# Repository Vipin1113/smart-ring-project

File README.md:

# Compact BLE-Based Smart Ring PCB for Health Monitoring and Gesture Detection

## Overview

This repository contains the complete KiCad project files, PCB layouts, schematic designs, manufacturing outputs, and documentation for a compact BLE-enabled Smart Ring developed for health monitoring and gesture detection applications.

The project focuses on wearable-oriented PCB miniaturization, low-power BLE communication, physiological sensing, gesture detection, RF-aware PCB implementation, and compact embedded system integration within a smart-ring-compatible form factor.

The implemented smart ring integrates:

- Nordic nRF52810 BLE SoC
- MAX30102 PPG Sensor
- ICM-42670 IMU Sensor
- Li-ion Charging Subsystem
- 3.3V Power Regulation
- Compact BLE Antenna Implementation

The final PCB dimensions achieved are:

22.8 mm × 9.6 mm

---

# Project Features

- Bluetooth Low Energy (BLE) Communication
- Heart Rate Monitoring
- SpO2 Monitoring
- Gesture Detection
- Motion Tracking
- Rechargeable Li-ion Battery Support
- Compact Wearable PCB Architecture
- RF Antenna Keepout Implementation
- Compact SWD Debugging Pads
- Exposed Charging Pads
- Backside PPG Sensor Placement
- 0402 Passive Component Integration

---

# Hardware Components

| Component | Manufacturer | Part Number |
|---|---|---|
| BLE MCU | Nordic Semiconductor | nRF52810-QCAA-T |
| PPG Sensor | Analog Devices | MAX30102 |
| IMU Sensor | TDK InvenSense | ICM-42670-P |
| Battery Charging IC | Microchip Technology | MCP73831-2-OT |
| 3.3V LDO | Texas Instruments | TPS78233DDC |
| 32 MHz Crystal | ECS Inc. | ECS-320-8-37-CKM-TR |
| 2.4 GHz Antenna | Johanson Technology | 2450AT18A100E |

---

# PCB Miniaturization and Design Evolution

The initial smart ring implementation utilized a larger PSoC BLE module-based architecture which occupied approximately:

30.4 mm × 12.0 mm

Although the module simplified BLE integration, it significantly increased PCB area and routing constraints.

To improve compactness and wearable compatibility, the architecture was migrated to the Nordic nRF52810 BLE SoC in a compact QFN package.

After multiple PCB iterations and routing optimizations, the final PCB dimensions were successfully reduced to:

22.8 mm × 9.6 mm

Major optimizations implemented include:

- Migration from BLE module to compact QFN SoC
- Compact exposed SWD pads
- Exposed charging pads
- Compact battery solder pads
- 0402 passive components
- Backside PPG placement
- RF antenna keepout implementation
- Routing optimization
- Compact subsystem placement
- Improved RF-aware PCB design

---

# PCB Design Highlights

## BLE Processing Subsystem

- Nordic nRF52810 BLE SoC
- ARM Cortex-M4
- BLE communication support
- Low-power wearable operation
- Compact QFN package

## Physiological Sensing

- MAX30102 optical PPG sensor
- Heart-rate monitoring
- SpO2 monitoring
- Backside wearable placement

## Motion Sensing

- ICM-42670 6-axis IMU
- Gesture detection
- Motion tracking
- Activity monitoring

## Power Management

- MCP73831 Li-ion charging IC
- TPS78233 low-noise LDO
- Rechargeable Li-ion battery support

## RF Subsystem

- 2.4 GHz chip antenna
- RF matching network
- Dedicated antenna keepout region

---

# Industrial-Level Miniaturization Considerations

Commercial smart-ring products generally utilize advanced packaging and PCB technologies including:

- WLCSP (Wafer-Level Chip Scale Packaging)
- HDI PCB technology
- Blind and buried vias
- Microvia routing
- Flexible PCB structures
- System-in-Package (SiP) integration
- Ultra-miniature PMIC solutions

Industrial wearable PMIC solutions analyzed during this project include:

- TI BQ25120A
- Nordic nPM1300
- Dialog DA9070
- MAX20345

These PMICs integrate:

- Battery charging
- Multiple LDOs
- Buck/boost converters
- Battery protection
- Fuel gauging

within a single compact package.

Although such PMICs can significantly reduce PCB area, they introduce substantially higher routing complexity and manufacturing difficulty. Therefore, a simpler discrete charging and regulation architecture was selected for the current implementation.

---

# Repository Structure

smart-ring-project/

├── README.md

├── LICENSE

├── smart_ring.kicad_pro

├── smart_ring.kicad_sch

├── smart_ring.kicad_pcb

├── Gerbers/

├── Images/

├── Report/

└── Datasheets/

---

# PCB Images

## Root Schematic

## PCB Layout and Routing

## 3D PCB Top View

## 3D PCB Bottom View

---

# Software Used

- KiCad 8.0
- GitHub
- Overleaf
- IEEE Conference LaTeX Template

---

# Verification and Validation

The implemented smart ring PCB successfully passed:

- Electrical Rule Check (ERC)
- Design Rule Check (DRC)
- Footprint Verification
- Connectivity Validation

The design additionally incorporates:

- RF-aware antenna keepout implementation
- Ground-plane optimization
- Compact routing methodology
- Wearable-oriented subsystem placement

---

# Future Improvements

Future improvements may include:

- Firmware implementation
- Gesture-recognition algorithms
- Mobile application development
- Flexible PCB implementation
- HDI PCB technology
- WLCSP packaging
- Advanced PMIC integration
- Battery-life optimization

---

# License

This project is licensed under the MIT License.

See the LICENSE file for details.

---

# Author

Vipin Kumar Mishra  
M.Tech ECE (VLSI)  
IIIT Bangalore

---

# Acknowledgement

This project was developed as part of the Electronic Systems Packaging course project focusing on compact wearable embedded system design, PCB miniaturization, RF-aware layout implementation, and smart wearable hardware development.

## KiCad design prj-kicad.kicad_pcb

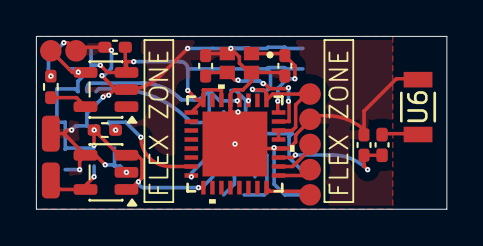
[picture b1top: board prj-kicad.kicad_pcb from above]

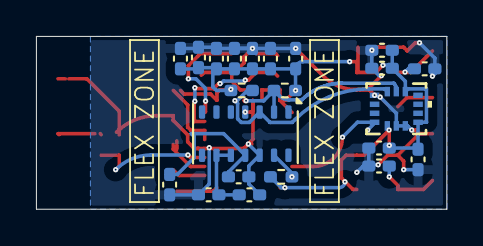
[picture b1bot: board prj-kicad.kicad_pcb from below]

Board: 2 copper layers, 22.8 x 9.6 mm, 38 parts (22 on the bottom side), 18 nets.

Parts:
C1, C2, C3, C15, C21: 1u; C_0402_1005Metric_Pad0.74x0.62mm_HandSolder
C4, C8, C17: 4.7u; C_0402_1005Metric_Pad0.74x0.62mm_HandSolder
C5, C6, C7, C10, C11, C14, C16, C18, C19, C22: 0.1u; C_0402_1005Metric_Pad0.74x0.62mm_HandSolder
C9: 0.8p; C_0402_1005Metric_Pad0.74x0.62mm_HandSolder
C12, C13: 12p; C_0402_1005Metric_Pad0.74x0.62mm_HandSolder
J1, J2: Conn_01x01; SolderWirePad_1x01_SMD_1x2mm
J3: Conn_01x02; Charging_Pad
J4: Conn_01x05; SWD_Pad
L1: 3.9n; L_0402_1005Metric_Pad0.77x0.64mm_HandSolder
R1: 40K; R_0402_1005Metric_Pad0.72x0.64mm_HandSolder
R4, R8: 10K; R_0402_1005Metric_Pad0.72x0.64mm_HandSolder
R6, R7: 4.7K; R_0402_1005Metric_Pad0.72x0.64mm_HandSolder
U1: MCP73831-2-OT; SOT-23-5
U2: NRF52810-QCAA-T; QFN32_5X5_NOR
U3: ICM-42670-P; LGA14_2.5X3X0.76_IVS
U4: TPS78233DDC; SOT-23-5
U5: MAX30102; Maxim_OLGA-14_3.3x5.6mm_P0.8mm
U6: 2450AT18A100E; 2450AT18A100E_JOT
Y2: ECS-320-8-37-CKM-TR; XTAL_ECS-320-8-37-CKM-TR

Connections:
/IMU/3p3V: C2.1, C4.1, C5.1, C6.2, C10.2, C11.2, C14.2, C17.2, C18.2, C19.2, C21.2, C22.2, J4.5, R4.1, R6.1, R7.1, R8.2, U1.3 (V_{BAT}), U2.1 (DEC1), U2.9 (VDD), U2.21 (DEC2), U2.22 (DEC3), U2.25 (VDD), U2.30 (DEC4), U2.32 (VDD), U3.5 (VDDIO), U3.8 (VDD), U3.12 (AP_CS), U4.1 (IN), U4.3 (EN)
/IMU/I2C.SCL: R6.2, U2.28 (P0.30/AIN6), U3.13 (AP_SCL/AP_SCLK), U5.2 (SCL)
/IMU/I2C.SDA: R7.2, U2.27 (P0.28/AIN4), U3.14 (AP_SDA/AP_SDIO/AP_SDI), U5.3 (SDA)
/IMU/IMU_INT: R4.2, U2.7 (P0.09), U3.4 (INT1/INT)
/MCU/PPG_INT: R8.1, U2.8 (P0.10), U5.13 (~INT)
/MCU/RESET: J4.1, U2.16 (P0.21/nRESET)
/MCU/SWDCLK: J4.2, U2.17 (SWDCLK)
/MCU/SWDIO: J4.3, U2.18 (SWDIO)
/PPG/VDD: C7.2, C15.2, U5.11 (VDD)
/PPG/VLED+: C8.2, C16.2, U5.9 (VLED+), U5.10 (VLED+)
/Pad-conn/CRG_5V: C1.2, J3.2, U1.4 (V_{DD})
/bat-conn/BatP: C3.1, J1.1, U4.5 (OUT)
GND: C1.1, C2.2, C3.2, C4.2, C5.2, C6.1, C7.1, C8.1, C9.2, C10.1, C11.1, C12.1, C13.1, C14.1, C15.1, C16.1, C17.1, C18.1, C19.1, C21.1, C22.1, J2.1, J3.1, J4.4, R1.2, U1.2 (V_{SS}), U2.20 (VSS), U2.29 (VSS), U2.33 (VSS), U3.1 (AP_SDO/AP_AD0), U3.6 (GND), U3.7 (FSYNC), U4.2 (GND), U4.4 (GND), U5.4 (PGND), U5.12 (GND), U6.2, Y2.2 (GND), Y2.4 (GND)
unnamed: L1.2, U6.1
unnamed: R1.1, U1.5 (PROG)
unnamed: C9.1, L1.1, U2.19 (ANT)
unnamed: C13.2, U2.23 (XC1), Y2.3 (OUT/IN)
unnamed: C12.2, U2.24 (XC2), Y2.1 (IN/OUT)

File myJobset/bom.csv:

"Reference","Value","Footprint","myMANUFACTURER","myMPN"
"C1","1u","Capacitor_SMD:C_0402_1005Metric_Pad0.74x0.62mm_HandSolder","Samsung Electro-Mechanics","CL05A105KO5NNNC"
"C2","1u","Capacitor_SMD:C_0402_1005Metric_Pad0.74x0.62mm_HandSolder","Samsung Electro-Mechanics","CL05A105KO5NNNC"
"C3","1u","Capacitor_SMD:C_0402_1005Metric_Pad0.74x0.62mm_HandSolder","Samsung Electro-Mechanics","CL05A105KO5NNNC"
"C4","4.7u","Capacitor_SMD:C_0402_1005Metric_Pad0.74x0.62mm_HandSolder","Samsung Electro-Mechanics","CL05A475MP5NRNC"
"C5","0.1u","Capacitor_SMD:C_0402_1005Metric_Pad0.74x0.62mm_HandSolder","Samsung Electro-Mechanics","CL05B104KP5NNNC"
"C6","0.1u","Capacitor_SMD:C_0402_1005Metric_Pad0.74x0.62mm_HandSolder","Samsung Electro-Mechanics","CL05B104KP5NNNC"
"C7","0.1u","Capacitor_SMD:C_0402_1005Metric_Pad0.74x0.62mm_HandSolder","Samsung Electro-Mechanics","CL05B104KP5NNNC"
"C8","4.7u","Capacitor_SMD:C_0402_1005Metric_Pad0.74x0.62mm_HandSolder","Samsung Electro-Mechanics","CL05A475MP5NRNC"
"C9","0.8p","Capacitor_SMD:C_0402_1005Metric_Pad0.74x0.62mm_HandSolder","Murata Electronics","GJM1555C1HR80WB01D"
"C10","0.1u","Capacitor_SMD:C_0402_1005Metric_Pad0.74x0.62mm_HandSolder","Samsung Electro-Mechanics","CL05B104KP5NNNC"
"C11","0.1u","Capacitor_SMD:C_0402_1005Metric_Pad0.74x0.62mm_HandSolder","Samsung Electro-Mechanics","CL05B104KP5NNNC"
"C12","12p","Capacitor_SMD:C_0402_1005Metric_Pad0.74x0.62mm_HandSolder","KEMET","C0402C120J5GACTU"
"C13","12p","Capacitor_SMD:C_0402_1005Metric_Pad0.74x0.62mm_HandSolder","KEMET","C0402C120J5GACTU"
"C14","0.1u","Capacitor_SMD:C_0402_1005Metric_Pad0.74x0.62mm_HandSolder","Samsung Electro-Mechanics","CL05B104KP5NNNC"
"C15","1u","Capacitor_SMD:C_0402_1005Metric_Pad0.74x0.62mm_HandSolder","Samsung Electro-Mechanics","CL05A105KO5NNNC"
"C16","0.1u","Capacitor_SMD:C_0402_1005Metric_Pad0.74x0.62mm_HandSolder","Samsung Electro-Mechanics","CL05B104KP5NNNC"
"C17","4.7u","Capacitor_SMD:C_0402_1005Metric_Pad0.74x0.62mm_HandSolder","Samsung Electro-Mechanics","CL05A475MP5NRNC"
"C18","0.1u","Capacitor_SMD:C_0402_1005Metric_Pad0.74x0.62mm_HandSolder","Samsung Electro-Mechanics","CL05B104KP5NNNC"
"C19","0.1u","Capacitor_SMD:C_0402_1005Metric_Pad0.74x0.62mm_HandSolder","Samsung Electro-Mechanics","CL05B104KP5NNNC"
"C21","1u","Capacitor_SMD:C_0402_1005Metric_Pad0.74x0.62mm_HandSolder","Samsung Electro-Mechanics","CL05A105KO5NNNC"
"C22","0.1u","Capacitor_SMD:C_0402_1005Metric_Pad0.74x0.62mm_HandSolder","Samsung Electro-Mechanics","CL05B104KP5NNNC"
"J1","Conn_01x01","Connector_Wire:SolderWirePad_1x01_SMD_1x2mm","",""
"J2","Conn_01x01","Connector_Wire:SolderWirePad_1x01_SMD_1x2mm","",""
"J3","Conn_01x02","SR_Library:Charging_Pad","",""
"J4","Conn_01x05","SR_Library:SWD_Pad","",""
"L1","3.9n","Inductor_SMD:L_0402_1005Metric_Pad0.77x0.64mm_HandSolder","Murata Electronics","LQG15HS3N9S02D"
"R1","40K","Resistor_SMD:R_0402_1005Metric_Pad0.72x0.64mm_HandSolder","Stackpole Electronics Inc","RNCF0402BTE40K0"
"R4","10K","Resistor_SMD:R_0402_1005Metric_Pad0.72x0.64mm_HandSolder","YAGEO","RC0402FR-0710KL"
"R6","4.7K","Resistor_SMD:R_0402_1005Metric_Pad0.72x0.64mm_HandSolder","YAGEO","RC0402FR-0710KL"
"R7","4.7K","Resistor_SMD:R_0402_1005Metric_Pad0.72x0.64mm_HandSolder","YAGEO","RC0402FR-0710KL"
"R8","10K","Resistor_SMD:R_0402_1005Metric_Pad0.72x0.64mm_HandSolder","YAGEO","RC0402FR-0710KL"
"U1","MCP73831-2-OT","Package_TO_SOT_SMD:SOT-23-5","Microchip Technology","MCP73831T-2ACI/OT"
"U2","NRF52810-QCAA-T","SR_Library:QFN32_5X5_NOR","Nordic Semiconductor ASA","NRF52810-QCAA-T"
"U3","ICM-42670-P","SR_Library:LGA14_2.5X3X0.76_IVS","TDK InvenSense","ICM-42670-P"
"U4","TPS78233DDC","Package_TO_SOT_SMD:SOT-23-5","Texas Instruments","TPS78233DDCT"
"U5","MAX30102","OptoDevice:Maxim_OLGA-14_3.3x5.6mm_P0.8mm","Analog Devices Inc./Maxim Integrated","MAX30102EFD+T"
"U6","2450AT18A100E","SR_Library:2450AT18A100E_JOT","Johanson Technology Inc.","2450AT18B0100001E"
"Y2","ECS-320-8-37-CKM-TR","SR_Library:XTAL_ECS-320-8-37-CKM-TR","ECS Inc.","ECS-320-10-37B-CKY-TR"

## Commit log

2026-05-14 SR.3dshapes/README.md
